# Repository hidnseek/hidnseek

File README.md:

# hidnseek
## The smart, Accurate GPS tracker on sigfox network

* true GPS localisation
* 3 axis Motion sensor
* Temperature and Pressure data logger
* Several months autonomous
* Rechargeable and monitored battery
* Firmware update with onchip USB interface
* Geo Fencing with [Apple iOS](https://itunes.apple.com/fr/app/hidnseek/id1014592720?mt=8) and [Android](https://play.google.com/apps/testing/com.hidnseek.hidnseek) Application
* GPIOs available for future extensions (i2c, Serial, ISP, Analog input, Digital)

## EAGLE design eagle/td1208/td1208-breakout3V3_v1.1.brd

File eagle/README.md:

# hidnseek

Eagle libray for the HidnSeek and droneRescue Projects

- MMA8653 Freescale Accelerometer
- Molex 47346 Micro USB Connector
- Atmega 328p MLF32 Package with small Thermal Pad
- Murata Super Capacitor DMF3 Series
- Taiyo Yuden Coin Cell Super Capacitor
- Telecom Design TD120x SigFox Internet of Things Modem
- TPS2513 Texas Instrument Current Limited USB Charger Controller
- TPS2294x Texas Instrument Current Limited Power Switch

# Telecom Design breakout board
schematic and layout for Eagle software

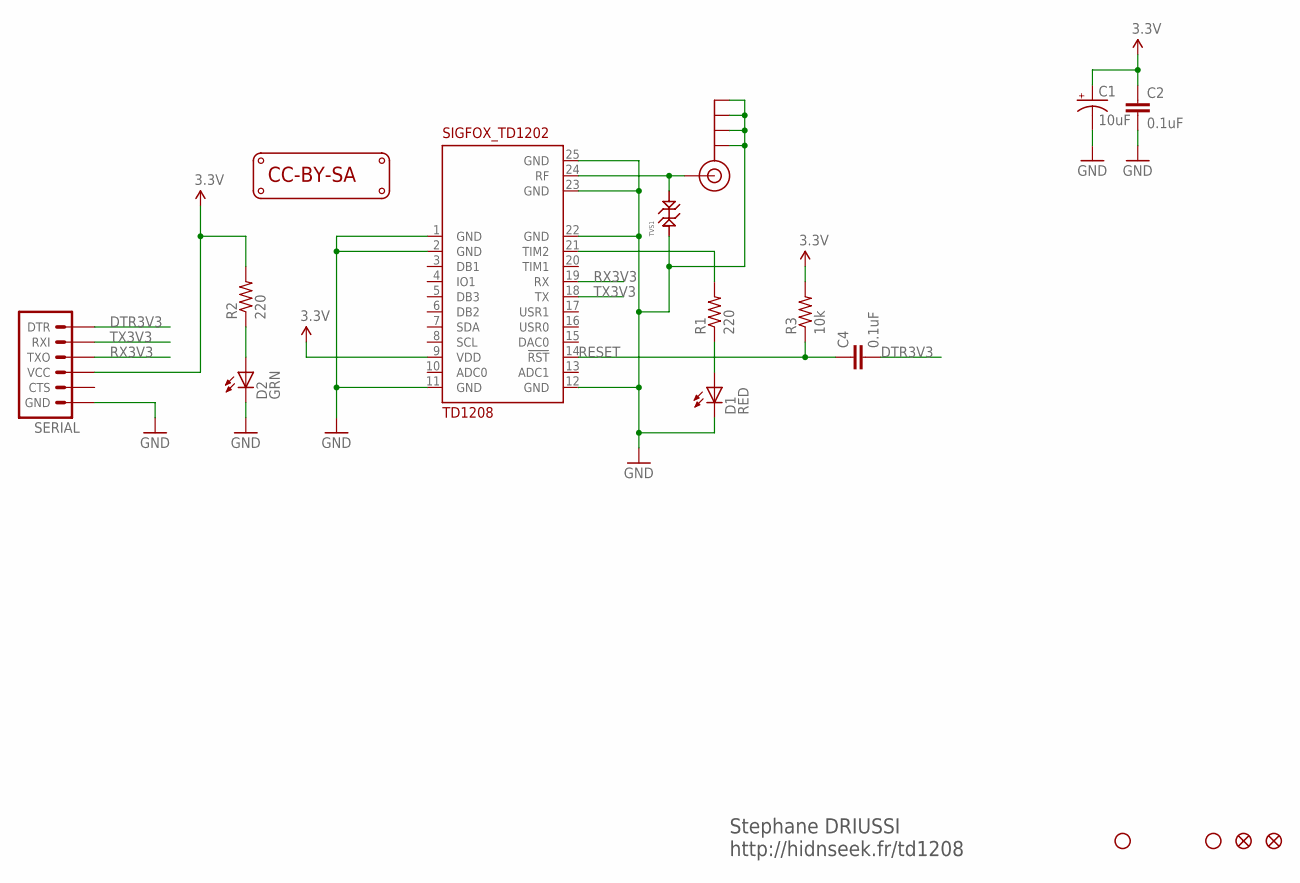
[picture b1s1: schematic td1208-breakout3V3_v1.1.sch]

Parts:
C1: 10uF; EIA3216; MOUSER# 74-293D106X96R3A2TE3
C2, C4: 0.1uF; 0402-CAP; MOUSER# 81-GRM155R60J104KA1D
D1: RED; CHIP-LED0603
D2: GRN; CHIP-LED0603
J$1: SMA_EDGE
LOGO1: LOGO_CC-BY-SA
R1, R2: 220; 0402-RES
R3: 10k; 0402-RES
SERIAL: ARDUINO_SERIAL_PROGRAMPTH; 1X06
TD1208: SIGFOX_TD1202; TD1202
TVS1: TVS_DIODESOD-923; SOD-923
U$5, U$11: STAND-OFF
U$7, U$16: FIDUCIAL1X2; FIDUCIAL-1X2

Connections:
3.3V: C1.A (+), C2.1, R2.2, R3.2, SERIAL.4 (VCC), TD1208.9 (VDD)
DTR3V3: C4.2, SERIAL.1 (DTR)
GND: C1.C (-), C2.2, D1.C, D2.C, J$1.GND@0 (GND), J$1.GND@1 (GND), J$1.GND@2 (GND), J$1.GND@3 (GND), SERIAL.6 (GND), TD1208.1 (GND), TD1208.2 (GND), TD1208.11 (GND), TD1208.12 (GND), TD1208.22 (GND), TD1208.23 (GND), TD1208.25 (GND), TVS1.P$1
unnamed: D2.A, R2.1
unnamed: J$1.SIG (SIGNAL), TD1208.24 (RF), TVS1.P$2
unnamed: R1.2, TD1208.21 (TIM2)
unnamed: D1.A, R1.1
RESET: C4.1, R3.1, TD1208.14 (!RST)
RX3V3: SERIAL.3 (TXO), TD1208.19 (RX)
TX3V3: SERIAL.2 (RXI), TD1208.18 (TX)

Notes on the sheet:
Stephane DRIUSSI http://hidnseek.fr/td1208

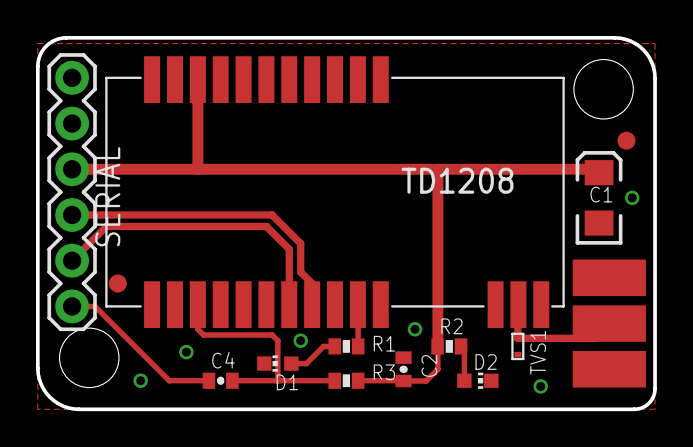
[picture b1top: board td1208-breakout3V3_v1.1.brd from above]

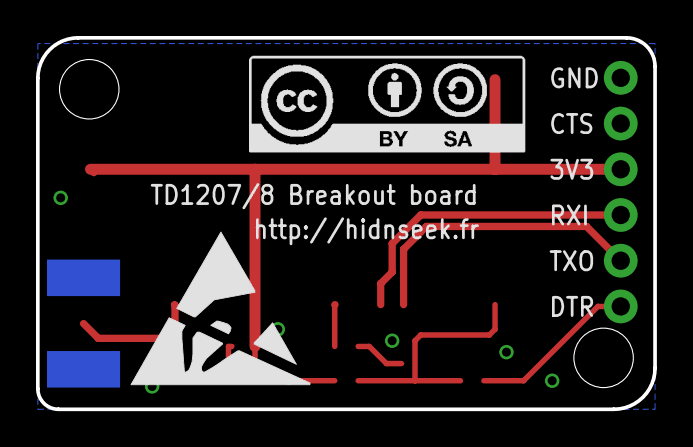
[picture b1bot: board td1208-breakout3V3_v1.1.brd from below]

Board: 2 copper layers, 34.3 x 20.6 mm, 18 parts (2 on the bottom side), 10 nets.

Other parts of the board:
U$1: ESD_10.00

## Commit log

2015-02-19 hidnSeek Eagle library
    Add freescale 3-Axis 10-bit Digital Accelerometer MMA8653
2015-12-02 Release A
2015-12-02 Initial
2015-12-09 Create gh-pages branch via GitHub
2015-12-15 Windows drivers
    windows driver from Thomas Fischl
2015-12-17 Add pictures
2016-01-03 HidnSeek Manuals
2016-01-03 Update Android Application Link
2016-01-03 firmware update for 3.28 board
    - Fix issue with modem ID that contain 73 value
    - Improve detection of airplane mode
    - Add sport mode feature
2016-01-16 Change barometer library
    This new library from seeedstudio save 1Kbytes in the flash program
    memory
2016-01-17 Fix Temp and Press update
2016-01-17 Clean repository
2016-01-20 Minor changes
2016-02-04 fix accel loop duration during GPS process
    The attendee period of the Accel measure during GPS reception is 8
    seconds, it was 16s on previous code.
2016-02-04 New speed algorithm for data reporting
    The speed limit has been changed from 201Km/h to 528Km/h (TGV speed is
    now correctly reported)
2016-02-12 Change librairie name
2016-02-12 Add Windows 8.1 and 10 USBasp driver
    Driver is now digitally signed.
2016-02-17 Add blink example
2016-02-17 Add Accelerometer example
    Led Red blink when motion, Led Blue blink otherwise
2016-02-20 Added files via upload
2016-02-20 Move hidnseek sketch to Examples directory
2016-02-27 Autostop demo
    To avoid battery issue, the demo stop itself after 51 seconds of non
    motion.
2016-02-27 Direct port manipulation
2016-02-27 add boot loader
2016-02-29 Rename Drivers/boards.txt to Drivers/Hardware/boards.txt
2016-02-29 Original example
2016-02-29 Add bootloader sources
2016-03-20 Minor changes
    comments formatted
2016-03-20 Minor change
    - Comments formatted
    - New calibration algorithm, reset calibration value after each restart
    - Remove 12mV to compensate battery internal resistance during charge
2016-03-20 Minor changes
    - Remove unused variables and definition
    - Change type values to proper scale
2016-03-20 Minor Changes
    - Comments reformatted
    - eeprom calls use defined ADDR instead of fixed number
2016-03-20 Minor Changes
    - Comments reformatted
    - Use direct port manipulation
    - make payload call in top of procedure
2016-03-20 Minor Change
    - Comments reformatted
    - Direct port manipulation
    - SportMode enabled
2016-03-20 Changes
    - Comments reformatted
    - Accelerate wait time to fix in good conditions
    - Payload procedure integrate all modes
2016-03-20 Changes
    - Comments reformatted
    - detectMotion is disabled if GPS speed > 15Km/h
    - new loop for NO_MOTION condition
2016-03-20 Add compiled code
2016-03-20 Update file
2016-03-23 Add php code
2016-03-31 fix include wire path
2016-04-07 fix active configuration
    Register REG2 need to be updated before entering in active mode
    Change to ODR at 6Hz and Low Power Mode, save 15uA
2016-04-23 Optimize library, code and power consumption
    Power consumption in sleep mode is reduced to 110uA that allow up to 3
    months more of autonomy.
2016-05-19 small update
    send message when speed is low
2016-05-19 add libraires
2016-05-19 cancel upload library
2016-05-19 create libraries zip
2016-06-10 New example for dog tracking
    This release activate dog tracking instead of sportMode. The tracker
    start to get the current position and store it has center of the
    geo-fencing.
2016-06-10 fix dog mode
    send message outside motion loop
2016-06-17 update airplane mode and fix SIGFOX lost message
2016-08-03 Corrected time for isReady()
    Time was originally set to 60000 milliseconds (1 minute) in the
    isReady() function. Unlicensed Frequency regulation limits protocol
    from transmitting more than 144 times per day. Increased value to
    600000 milliseconds (10 minutes).
2016-08-18 I2C library from Wayne Truchsess
2016-08-18 Change i2c calls
    Change i2c calls to use Wayne Truchsess I2C library
2016-08-18 Add new board
    3.28B hardware have by default battery charge current set to 40mA.
    This can be change after boot to 100mA for USB connection
    3.28 hardware have by default battery charge current to 100mA and can be changed to 250mA for wall adapter only.
2016-08-21 fix cap
    add accurate cap when altitude < 16 meters
2016-08-21 see line 72 for ST1A boards
2016-08-21 support for external hex
2017-02-09 fix compile issue
2017-02-09 fix issue in replay time
    Replay time is wrong after 5:12pm UTC
2017-02-09 fix compilation issue
2017-02-09 fix altitude for value greater than 4096 meters
2017-02-15 fix comment around pin3 and pin8
2017-02-16 Windows 10
2017-06-23 fix option message type 3 missing
2017-09-07 Update and rename HidnSeek_v3_28_beta.hex to HidnSeek_v3_28B.hex
    Last release of the revision B
2017-09-07 Update HidnSeek_v3_28.hex
    Revision A of the electonic board
2017-09-07 Update HidnSeek_v3_28.hex for RevA board
2017-09-07 Update and rename firmware for RevB board
2017-09-29 add uncompress altitude function
2019-06-26 production firmware
2020-03-28 return int16_t for high resolution mode
2020-03-28 begin() return true if mems connected

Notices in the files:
eagle/README.md:
https://github.com/hidnseek/hidnseek/blob/master/eagle/cc-by-nc-sa.png
